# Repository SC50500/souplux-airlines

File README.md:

# Souplux Airlines!
A name badge that introduces who I am with the theme of travel because I'm traveling this summer!
[Made for FALLOUT's in-person event]

# Description
For this name badge, I kept the PCB quite simple, using a XIAO ESP32-C3 to process how many times each button on the PCB is clicked and program it to turn on. Each light represents a different destination that I'm traveling to this year after Fallout in Shenzhen.

# Sentiment
I love traveling and visiting new places, so I thought, "What better way to introduce myself than to show where I'm traveling this summer?"

# Schematics (Yippee!!)

# PCB :3

# 3D View

# Build & Design
1. Using the tamagotchi tutorial made by @TaniWanKenobi (located on the Fallout docs & resources site), connect four switches and four LEDs to pins 1-8 on the MCU respectively.
2. Place all of the buttons and LEDs on the F.Cu and place the rest of the components (resistors, MCU, & battery) on the B.Cu
3. Add the design in the files attached & rearrange the buttons to match the PCB design.
4. And that's it! It's as simple as that ^^

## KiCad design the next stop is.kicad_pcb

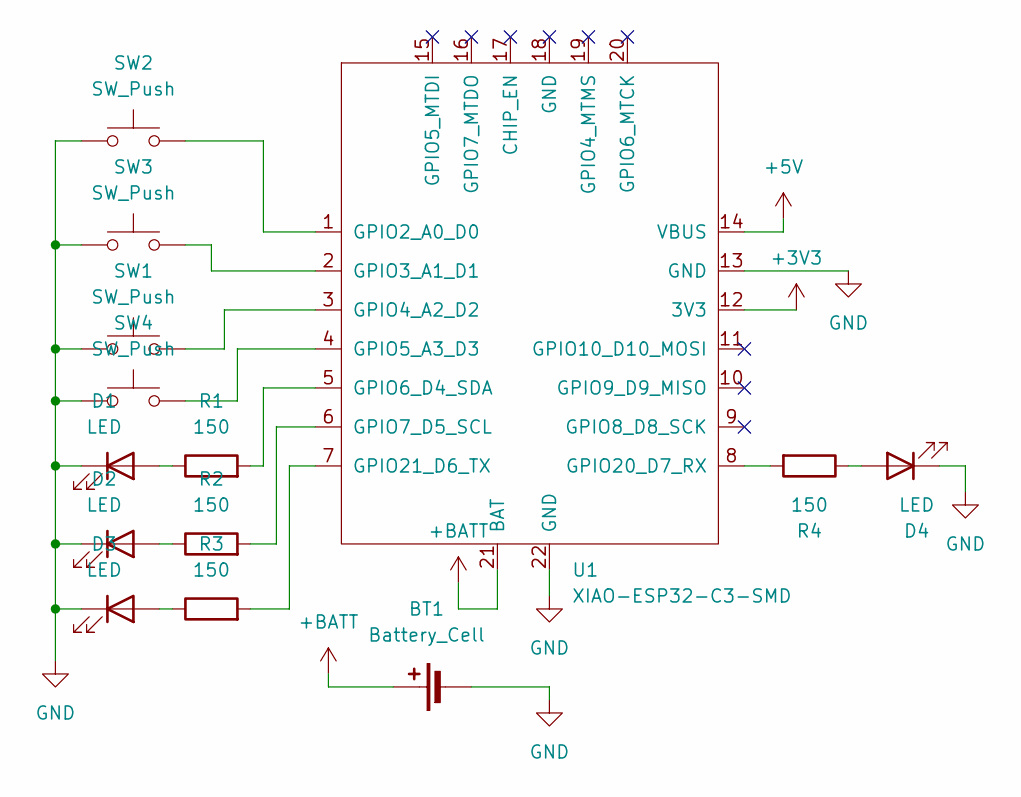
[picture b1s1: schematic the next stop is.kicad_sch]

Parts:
BT1: Battery_Cell; PinHeader_1x02_P2.54mm_Vertical
D1, D2, D3, D4: LED; LED_D3.0mm
R1, R2, R3, R4: 150; RES-TH_BD2.2-L6.5-P10.50-D0.6
SW1, SW2, SW3, SW4: SW_Push; SW-TH_4P-L4.5-W4.5-P3.00-LS4.8
U1: XIAO-ESP32-C3-SMD; XIAO-ESP32-C3-DIP-SMD

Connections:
+3V3: U1.12 (3V3)
+5V: U1.14 (VBUS)
+BATT: BT1.1 (+), U1.21 (BAT)
GND: BT1.2 (-), D1.1 (K), D2.1 (K), D3.1 (K), D4.1 (K), SW1.1, SW2.1, SW3.1, SW4.1, U1.13 (GND), U1.22 (GND)
unnamed: D1.2 (A), R1.1
unnamed: D2.2 (A), R2.1
unnamed: D3.2 (A), R3.1
unnamed: D4.2 (A), R4.1
unnamed: SW2.2, U1.1 (GPIO2_A0_D0)
unnamed: SW3.2, U1.2 (GPIO3_A1_D1)
unnamed: SW1.2, U1.3 (GPIO4_A2_D2)
unnamed: SW4.2, U1.4 (GPIO5_A3_D3)
unnamed: R1.2, U1.5 (GPIO6_D4_SDA)
unnamed: R2.2, U1.6 (GPIO7_D5_SCL)
unnamed: R4.2, U1.8 (GPIO20_D7_RX)
unnamed: R3.2, U1.7 (GPIO21_D6_TX)

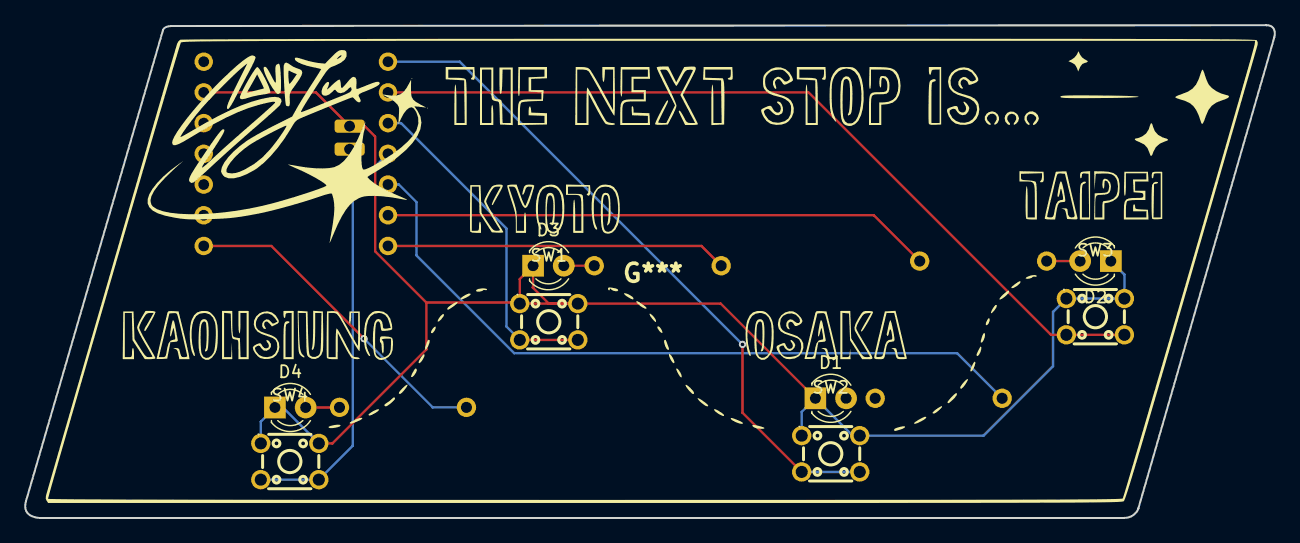
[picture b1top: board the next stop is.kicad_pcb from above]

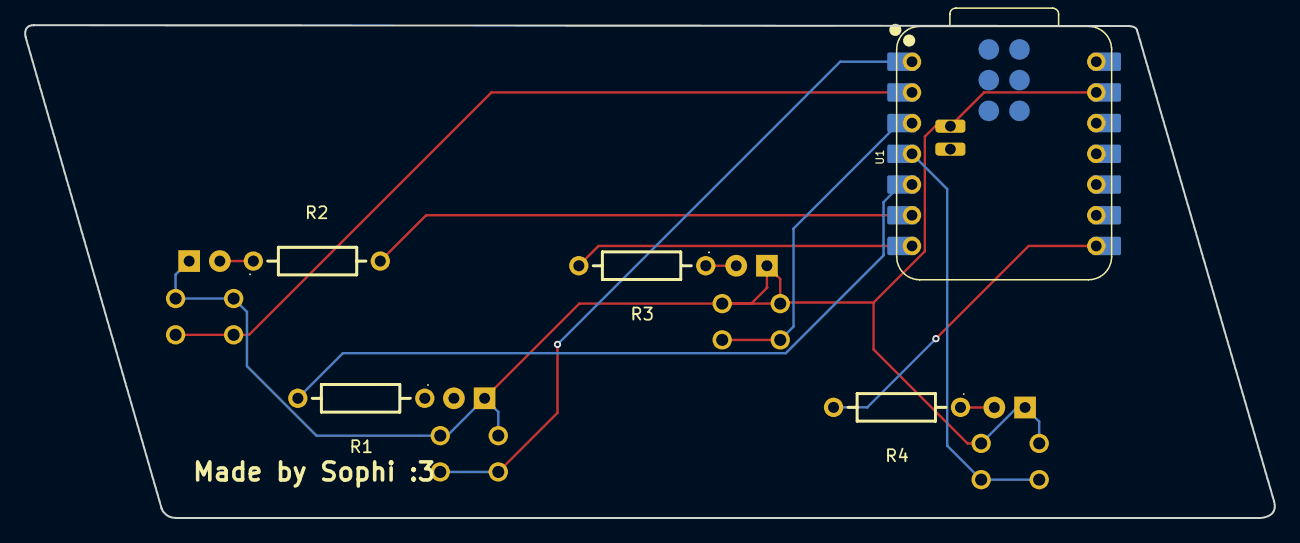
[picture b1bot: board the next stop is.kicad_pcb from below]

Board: 2 copper layers, 103.4 x 40.8 mm, 13 parts (5 on the bottom side), 13 nets.
